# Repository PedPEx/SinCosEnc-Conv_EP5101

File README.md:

# EP5101 SinCos $11µA_{PP}$ and $1V_{PP}$ encoder/glass scale to TTL (RS422 compliance) converter (ARCHIVED)

This repo is no longer maintained. There is no reason to interface $11µA_{PP}$ sensors with the help of this PCB and an EtherCAT-based incremental encoder input module - like an EL5101 or an EP5101. Due to the cost of one assembled converter PCB (~30€ total), it is a competitive alternative to the original iC-Haus EVAL board of the [iC-NV](https://www.ichaus.de/product/ic-nv/) and the Heidenhain EXEs, if used with other RS422 or TTL encoder inputs.

If you are planning on using EtherCAT as your system bus, use the [documented process here on how to modify an EL5021 terminal](https://github.com/PedPEx/EL5021_multi-signal-mod) instead (which internally uses an iC-Haus IC similar to this project).

In my [bachelor's thesis](https://pedpex.github.io/Maho400E-LinuxCNC/docs/bachelors_thesis.pdf) I updated the old 0.9.6/0.9.7 version of the PCB a little, so that it better tolerates EMI conditions. As I was not very happy with the improvements in v0.9.8, it was never officially pushed. After further inspection, starting from scratch would be the better decision in order to get better EMI ratings. Additionally, the shielding of the EP5101-0011 is floating, which is also not the desired state. Since the alternative is far cheaper, a 4-layer redesign is not worthwhile, and as the new board is no longer used, this project will no longer be maintained and will therefore be archived.

PCB version v0.9.6 was fully working and successfully tested. Version v0.9.8 was never produced nor tested.
This board is provided as is - unfinished and untested. Productive use is explicitly not recommended! Further rework is required. No support is offered for it. The project will be left as is.

---

<details>
  <summary>Old README content</summary>
  
# EP5101 SinCos $11µA_{PP}$ and $1V_{PP}$ encoder/glass scale to TTL (RS422 compliance) converter (WIP!)
This interface board is designed to convert a encoder signal with $11µA_{PP}$ (peak-peak) or $1V_{PP}$ signal to TTL with a [iC-Haus iC-NV](https://www.ichaus.de/product/ic-nv/) be used with a [Beckhoff EP5101](https://www.beckhoff.com/de-de/produkte/i-o/ethercat-box/epxxxx-industriegehaeuse/ep5xxx-winkel-wegmessung/ep5101-0011.html?) for example in LinuxCNC.

Assembly concept (with old potentiometer and RJ45 jack):

Single encoder input             |  Three encoder inputs with terminal blocks
:-------------------------:|:-------------------------:
  |  

PCB:\

## ToDo
- ✅ finished prototype PCB (v0.9.6)
- ✅ working conversion
- ✅ tested intensively with [LS403](docs/Heidenhain-LS-403-LS-403C.pdf) and [EP5101](https://www.beckhoff.com/de-de/produkte/i-o/ethercat-box/epxxxx-industriegehaeuse/ep5xxx-winkel-wegmessung/ep5101-0011.html?)

## Powering, connectors and signals
The board needs no seperate supply voltage and is fully powered by the 5V supply of the EP5101. The green led indicates a working 5V sensor rail. Supported input signals are $11µA_{PP}$ (standard) and $1V_{PP}$. By default, the output is a differential RS422 TTL-encoder signal. In that case, component ```U2``` ([AM26LS31](https://www.ti.com/product/de-de/AM26LS31) - Differential Line Driver) is populated on the PCB. By removing ```U2``` and either manualy shorting ```JP1 - JP6``` or populating ```R5 - R10``` with $0 \Omega$ resistors (manual adjustment of BOM is required). 

Because the [Beckhoff EL5101](https://www.beckhoff.com/de-de/produkte/i-o/ethercat-klemmen/el5xxx-winkel-wegmessung/el5101.html) is way more common than the EP5101, a 3D printable holder is in the works and will also be added to the repo, as soon as it has reached a usable state. 

There could also be a master-PCB, which would be used in standalone use or with a Mesa FPGA board. This master-PCB would need a 24V to 5V regulator and three DSUB15 female connectors in order to connect to the interpolator PCBs and three connectors (RJ45 eventually?) to connect the TTL signals to the Mesa encoder inputs. A integrated DIN rail mount would make mounting easy. In case there is interest in such a board, feel free to open a issue and i will design one. 

## Mounting adaptor
There is a DIN-rail mounting adaptor avaliable, which is used to mount a M23 male connector and a EP5101 onto a 35 mm standard rail. You can find the [files to 3D print](https://than.gs/m/1345234) it yourself over on my Thangs-account.

## Config switches
Pretty much everything of the [iC-NV](https://www.ichaus.de/product/ic-nv/) is configurable through config switches and a potentiometer ($50 k\Omega$). The two most common configs are printed on the backside of the PCB

## Terminal blocks, connectors and pinouts
The shielded DSUB15 port has the following pinout:

| pin DSUB15 | usage/signal |
| :---  | :---      |
| 1     | DifSig_A+ / TTL_A   |
| 2     | GND   |
| 3     | DifSig_B+ / TTL_B   |
| 4     | 5V VCC   |
| 5     | n.c.   |
| 6     | n.c.       |
| 7     | DifSig_C- / TTL_GND  |
| 8     | n.c.  |
| 9     | DifSig_A- / TTL_GND  |
| 10    | GND  |
| 11    | DifSig_B- / TTL_GND  |
| 12    | 5V VCC  |
| 13    | E̅R̅R̅O̅R̅ out |
| 14    | DifSig_C+ / TTL_B  |
| 15    | n.c.  |

The shielded RJ45 port has the following pinout:

| pin RJ45 | usage/signal |
| :---  | :---      |
| 1     | In_SIN+   |
| 2     | In_SIN-   |
| 3     | +5 V      |
| 4     | In_COS+   |
| 5     | In_COS-   |
| 6     | GND       |
| 7     | In_ZERO+  |
| 8     | In_ZERO-  |

The 8 pin male-header J2 has the following pinout (standard Heidenhain pinout):

```
                        odd pins  |  even pins
╔════╦════╗             ----------|------------
║  1 ║  2 ║════════      In_SIN+  |  In_SIN-
╠════╬════╣                       |
║  3 ║  4 ║════════      In_COS+  |  In_COS-
╠════╬════╣                       |
║  5 ║  6 ║════════     In_ZERO+  |  In_ZERO-
╠════╬════╣                       |
║  7 ║  8 ║════════          GND  |  Shield
╠════╬════╣                       |
║  9 ║ 10 ║════════          +5V  |  Shield
╚════╩════╝
```

*Note:*\
DO ONLY CONNECT ONE SENSOR INPUT! NEVER USE THE PINHEADER AND RJ45 SIMULTANEOUSLY!

## Analog Frontend / Signal Conditioning Stage
After reaching out to iC-Haus' support for some details about the needed analog frontend for $11 µA_{PP}$ sensors, i got some details on how to implement it. A really nice solution which works with $1 V_{PP}$ as well as $11 µA_{PP}$ signals was documented in the [iC-NQC datasheet (page 28)](docs/iC-NQC_datasheet_E2en.pdf). This exact signal conditioning stage was implemented for all three stages. By shorting each ```CHx_JP1``` you can connect the $120 \Omega$ termination resistor to the input side of the input stage and by that set the device to its $1 V_{PP}$ operating mode.

## Usage/Software
This interface board is meant to be used in combination with the [Beckhoff EP5101 module](hhttps://www.beckhoff.com/de-de/produkte/i-o/ethercat-box/epxxxx-industriegehaeuse/ep5xxx-winkel-wegmessung/ep5101-0011.html?). The EP5101 is then used by the [LinuxCNC software](https://linuxcnc.org/) to read e.g. Heidenhain LS403 glass scales on a Maho MH400E.

A adaptor/mounting kit is in the works, that this project can also be used with [Beckhoffs EL5101](https://www.beckhoff.com/de-de/produkte/i-o/ethercat-klemmen/el5xxx-winkel-wegmessung/el5101.html) encoder inputs.

Also keep in mind that you need a sufficiently sized counter. For most retrofits a 16 bit wide counter will not cut it. 
Quick example:
```math 
n_{min} = \log_2 \left(\frac{range\_of\_motion}{axis\_resolution}\right) = \log_2 \left(\frac{400 mm}{1 \mu m}\right) = 18.61 bit \approx \textbf{19 bit > 16 bit}
```
In addition to the resolution you you also need to check the cutoff frequency (maximum input frequency) of the encoder input. The ```EP5101-0011``` for example is limited to $1.0 MHz$ (that's really high, especally in fourfold evaluation mode). For a resolution of $1 µm$ the maximum axis speed is:
```math
v_{max\_EC-Input} = \frac{resolution\_of\_sensor}{interpolation\_factor \cdot quadratur\_encoder\_input} \cdot cutoff\_frequency = {overall\_resolution \cdot cutoff\_frequency} = \frac{20µm}{5 \cdot 4} \cdot 1.0 MHz = 1µm \cdot 1.0 MHz = 1.0 \frac{m}{s}
```
The same calculation needs to be done with the input side of the IC ```iC-NV```. The cutoff frequency depends on the used gain. For a $gain = 4$ the manual states a $fin_{MAX}=200 kHz$ (for RCLK = VCC).
```math
v_{max\_IC-Input} = resolution\_of\_sensor \cdot cutoff\_frequency_{IC} = 20µm \cdot 200 kHz = 4.0 \frac{m}{s}
```
The lower value of the two calculated velocities, $v_{max\_{EC-Input}} = 1.0 \frac{m}{s}$ and $v_{max\_IC-Input} = 4.0 \frac{m}{s}$, is $1.0 \frac{m}{s}$. This represents the maximum permissible speed for the corresponding axis and must not be exceeded!

## Documentation
All docs can be found in the [docs folder](docs/).

## Online Preview / BOM
[Detailed schematics preview](https://kicanvas.org/?github=https%3A%2F%2Fgithub.com%2FPedPEx%2FSinCosEnc-Conv_EP5101) (KiCanvas)

[Online BOM](https://htmlpreview.github.io/?https://raw.githubusercontent.com/PedPEx/SinCosEnc-Conv_EP5101/master/bom/webviewer-BOM.html)

[PDF schematics (v0.9.6)](https://github.com/PedPEx/SinCosEnc-Conv_EP5101/blob/master/SinCosEnc-Converter_EP5101-0011_schematic_v0.9.6.pdf)

## *Note*
The pictures were rendered with the help of Blender and the [pcb2blender](https://github.com/30350n/pcb2blender) plugin and the HTML BOM was created with [InteractiveHtmlBom](https://github.com/openscopeproject/InteractiveHtmlBom).

</details>

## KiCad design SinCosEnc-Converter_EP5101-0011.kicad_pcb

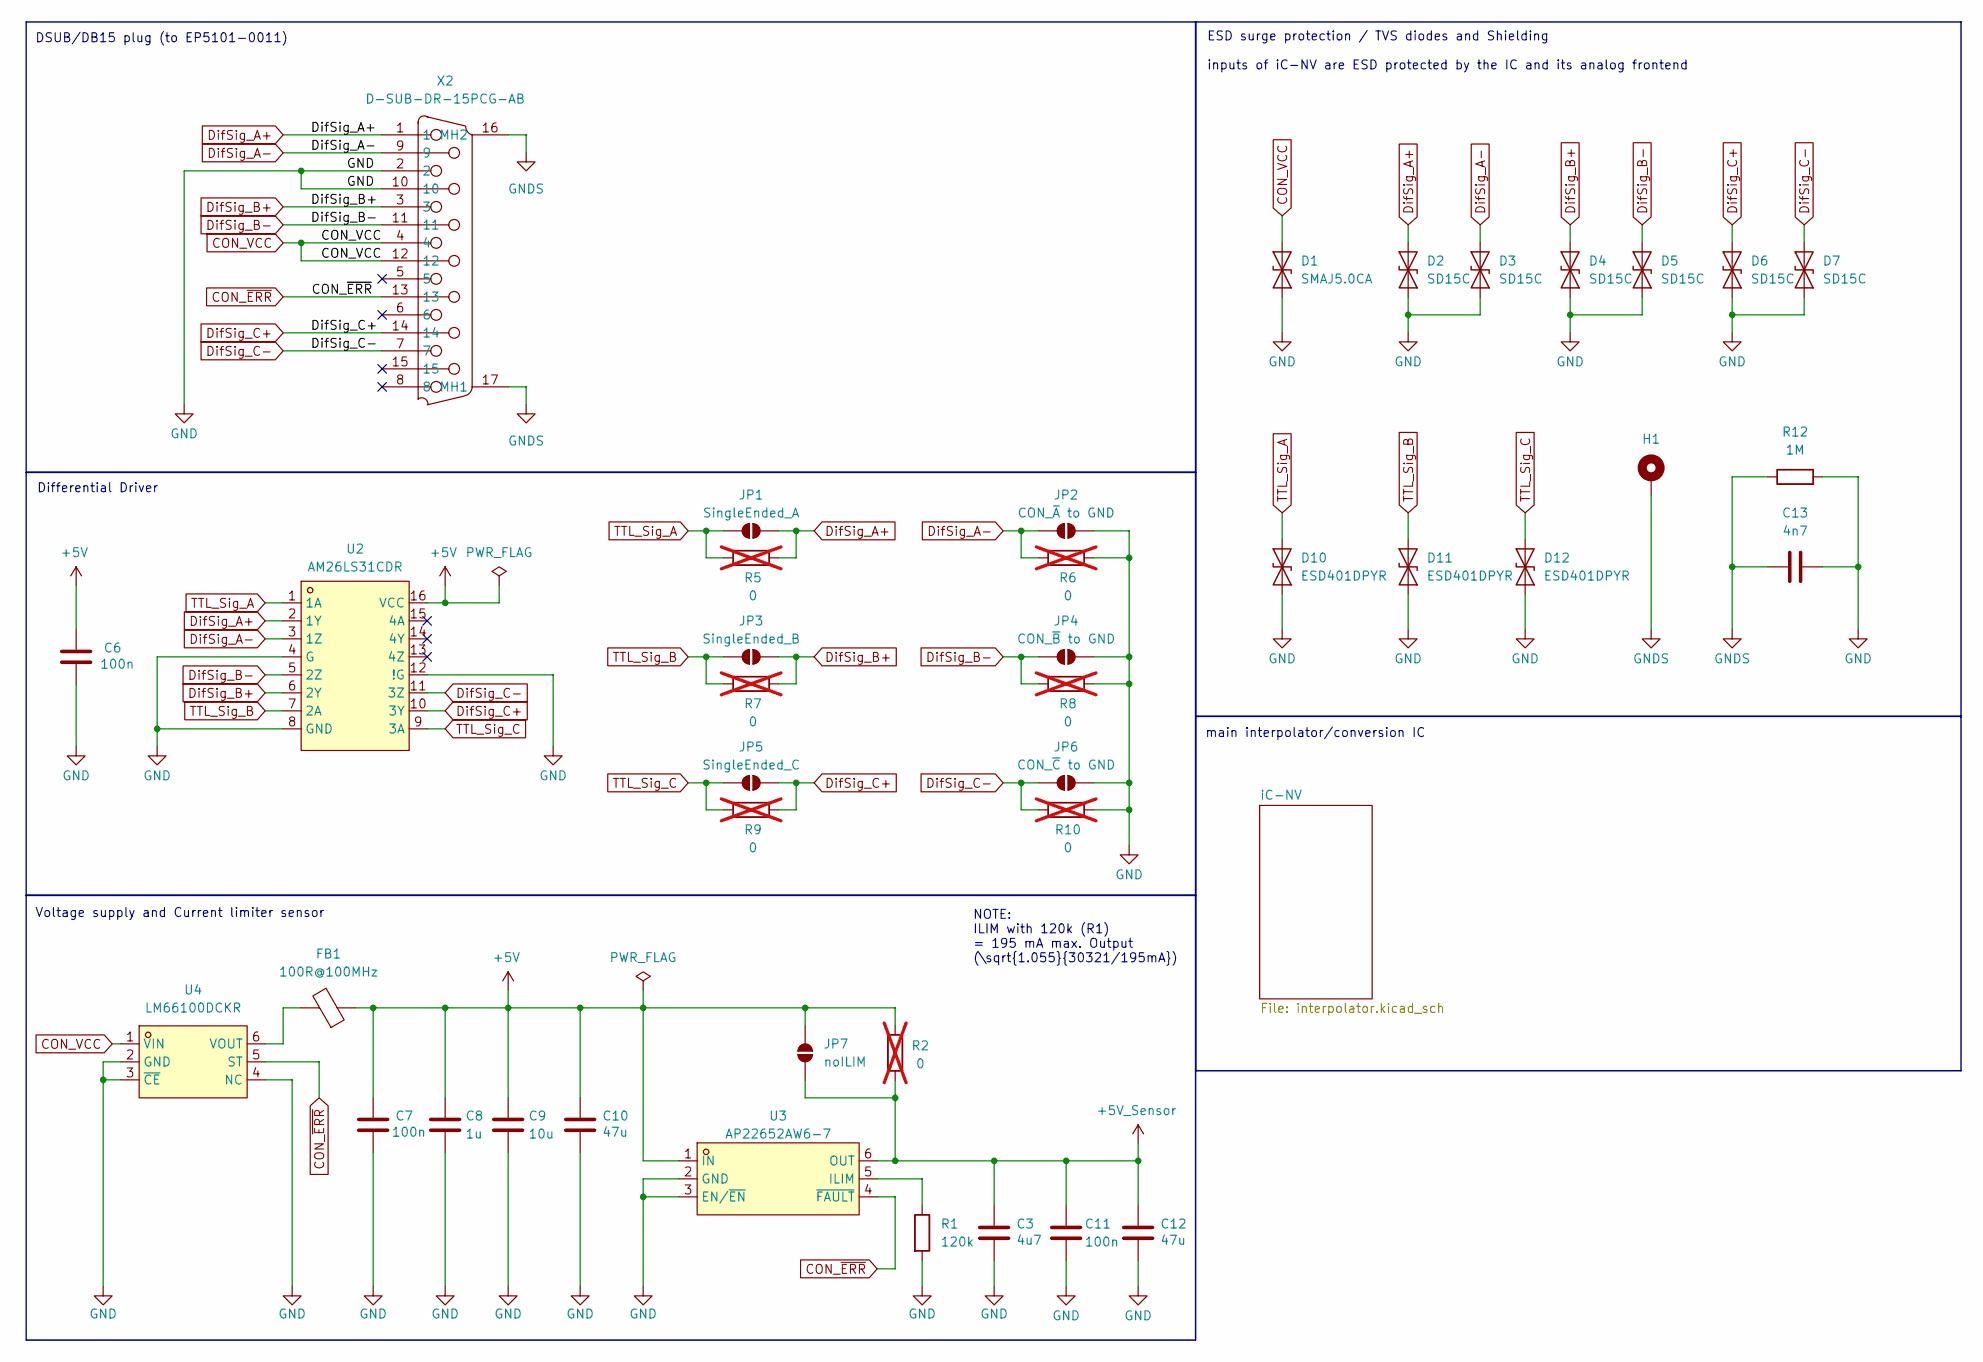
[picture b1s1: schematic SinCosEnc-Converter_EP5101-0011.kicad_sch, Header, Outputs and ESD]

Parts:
C3: 4u7; C_0603_1608Metric; LCSC Part C1705
C6, C7, C11: 100n; C_0603_1608Metric; LCSC Part C14663
C8: 1u; C_0603_1608Metric; LCSC Part C15849
C9: 10u; C_0603_1608Metric; LCSC Part C91606
C10, C12: 47u; C_1206_3216Metric; LCSC Part C94034
C13: 4n7; C_1808_4520Metric; LCSC Part C161101
D1: SMAJ5.0CA; D_SMA; LCSC Part C83324
D2, D3, D4, D5, D6, D7: SD15C; D_SOD-323; LCSC Part C207245
D10, D11, D12: ESD401DPYR; Texas_DPY0002A_0.6x1mm_P0.65mm; LCSC Part C1974752
FB1: 100R@100MHz; L0603; LCSC Part C107332
H1: MountingHole_Pad; MountingHole_3.2mm_M3_DIN965_Pad_TopBottom
JP1: SingleEnded_A; SolderJumper-2_P1.3mm_Open_RoundedPad1.0x1.5mm
JP2: CON_~{A} to GND; SolderJumper-2_P1.3mm_Open_RoundedPad1.0x1.5mm
JP3: SingleEnded_B; SolderJumper-2_P1.3mm_Open_RoundedPad1.0x1.5mm
JP4: CON_~{B} to GND; SolderJumper-2_P1.3mm_Open_RoundedPad1.0x1.5mm
JP5: SingleEnded_C; SolderJumper-2_P1.3mm_Open_RoundedPad1.0x1.5mm
JP6: CON_~{C} to GND; SolderJumper-2_P1.3mm_Open_RoundedPad1.0x1.5mm
JP7: noILIM; SolderJumper-2_P1.3mm_Open_RoundedPad1.0x1.5mm
R1: 120k; R_0603_1608Metric; LCSC Part C22954
R2, R5, R6, R7, R8, R9, R10: 0; R_0603_1608Metric; not fitted
R12: 1M; R_2010_5025Metric; LCSC Part C2779367
U2: AM26LS31CDR; SOIC-16_L9.9-W3.9-P1.27-LS6.0-BL; LCSC Part C6179
U3: AP22652AW6-7; SOT-23-6_L2.9-W1.6-P0.95-LS2.8-BL; LCSC Part C5329413
U4: LM66100DCKR; SC-70-6_L2.0-W1.3-P0.65-LS2.1-BL; LCSC Part C2869734
X2: D-SUB-DR-15PCG-AB; DSUB-TH_D-SUB-DR-15PCG-AB; LCSC Part C19077347

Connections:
+5V: C6.2, C7.2, C8.2, C9.2, C10.2, FB1.1, JP7.2 (B), R2.2, U2.16 (VCC), U3.1 (IN); also elsewhere on the board
+5V_Sensor: C3.2, C11.2, C12.2, JP7.1 (A), R2.1, U3.6 (OUT); also elsewhere on the board
CON_VCC: D1.2 (A2), U4.1 (VIN), X2.4, X2.12
CON_~ERR: U3.4 (~FAULT), U4.5 (ST), X2.13; also elsewhere on the board
DifSig_A+: D2.2 (A2), JP1.2 (B), R5.1, U2.2 (1Y), X2.1
DifSig_A-: D3.2 (A2), JP2.1 (A), R6.2, U2.3 (1Z), X2.9
DifSig_B+: D4.2 (A2), JP3.2 (B), R7.1, U2.6 (2Y), X2.3
DifSig_B-: D5.2 (A2), JP4.1 (A), R8.2, U2.5 (2Z), X2.11
DifSig_C+: D6.2 (A2), JP5.2 (B), R9.1, U2.10 (3Y), X2.14
DifSig_C-: D7.2 (A2), JP6.1 (A), R10.2, U2.11 (3Z), X2.7
GND: C3.1, C6.1, C7.1, C8.1, C9.1, C10.1, C11.1, C12.1, C13.2, D1.1 (A1), D2.1 (A1), D3.1 (A1), D4.1 (A1), D5.1 (A1), D6.1 (A1), D7.1 (A1), D10.1 (A1), D11.1 (A1), D12.1 (A1), JP2.2 (B), JP4.2 (B), JP6.2 (B), R1.2, R6.1, R8.1, R10.1, R12.2, U2.4 (G), U2.8 (GND), U2.12 (!G), U3.2 (GND), U3.3 (EN/~EN), U4.2 (GND), U4.3 (~CE), U4.4 (NC), X2.2, X2.10; also elsewhere on the board
GNDS: C13.1, H1.1, R12.1, X2.16 (MH2), X2.17 (MH1); also elsewhere on the board
unnamed: R1.1, U3.5 (ILIM)
unnamed: FB1.2, U4.6 (VOUT)
TTL_Sig_A: D10.2 (A2), JP1.1 (A), R5.2, U2.1 (1A); also elsewhere on the board
TTL_Sig_B: D11.2 (A2), JP3.1 (A), R7.2, U2.7 (2A); also elsewhere on the board
TTL_Sig_C: D12.2 (A2), JP5.1 (A), R9.2, U2.9 (3A); also elsewhere on the board

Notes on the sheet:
main interpolator/conversion IC
NOTE: ILIM with 120k (R1) = 195 mA max. Output (\sqrt{1.055}{30321/195mA})
ESD surge protection / TVS diodes and Shielding inputs of iC-NV are ESD protected by the IC and its analog frontend
Voltage supply and Current limiter sensor
DSUB/DB15 plug (to EP5101-0011)
Differential Driver

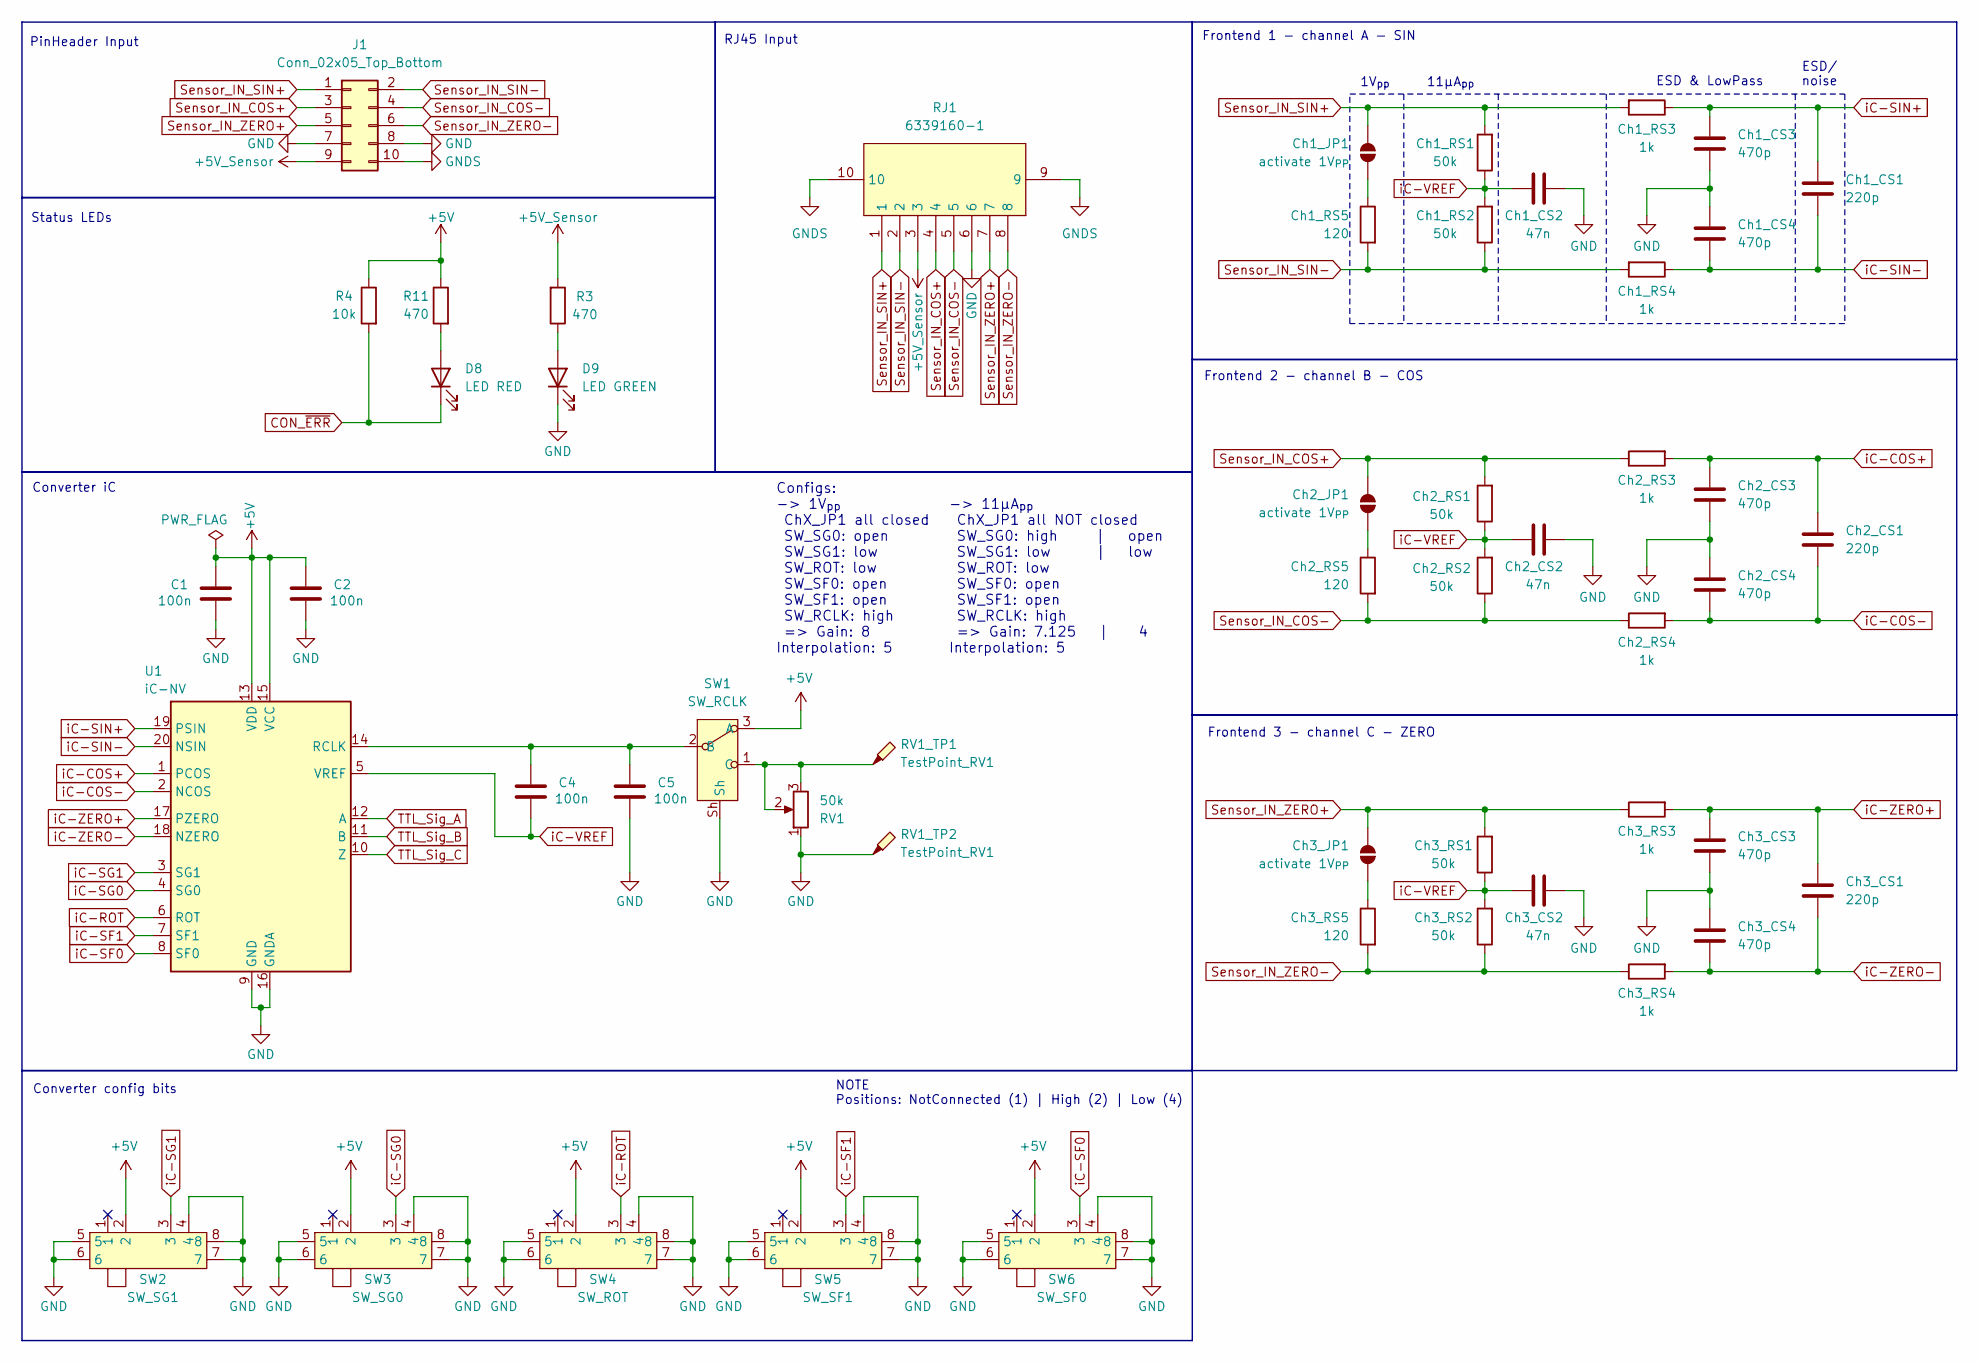
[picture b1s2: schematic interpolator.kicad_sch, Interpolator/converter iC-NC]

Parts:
C1, C2, C4, C5: 100n; C_0603_1608Metric; LCSC Part C14663
Ch1_CS1, Ch2_CS1, Ch3_CS1: 220p; C_0603_1608Metric; LCSC Part C107081
Ch1_CS2, Ch2_CS2, Ch3_CS2: 47n; C_0603_1608Metric; LCSC Part C1622
Ch1_CS3, Ch1_CS4, Ch2_CS3, Ch2_CS4, Ch3_CS3, Ch3_CS4: 470p; C_0603_1608Metric; LCSC Part C22396
Ch1_JP1, Ch2_JP1, Ch3_JP1: activate 1V_{PP}; SolderJumper-2_P1.3mm_Open_RoundedPad1.0x1.5mm
Ch1_RS1, Ch1_RS2, Ch2_RS1, Ch2_RS2, Ch3_RS1, Ch3_RS2: 50k; R_0603_1608Metric; LCSC Part C861451
Ch1_RS3, Ch1_RS4, Ch2_RS3, Ch2_RS4, Ch3_RS3, Ch3_RS4: 1k; R_0603_1608Metric
Ch1_RS5, Ch2_RS5, Ch3_RS5: 120; R_0603_1608Metric; LCSC Part C22787
D8: LED RED; LED_0603_1608Metric; LCSC Part C2986060
D9: LED GREEN; LED_0603_1608Metric; LCSC Part C2986059
J1: Conn_02x05_Top_Bottom; PinHeader_2x05_P2.54mm_Horizontal; LCSC Part C492433
R3, R11: 470; R_0603_1608Metric
R4: 10k; R_0603_1608Metric
RJ1: 6339160-1; RJ45-SMD_6339160-1; LCSC Part C125076
RV1: 50k; Potentiometer_Bourns_3266X_Horizontal; LCSC Part C780222
RV1_TP1: TestPoint_RV1; TestPoint_THTPad_2.0x2.0mm_Drill1.0mm
RV1_TP2: TestPoint_RV1; TestPoint_THTPad_D2.0mm_Drill1.0mm
SW1: SW_RCLK; SW-SMD_XKB_SS-3292S-L2-W; LCSC Part C2884756
SW2: SW_SG1; SW-SMD_MSK13C02-BB; LCSC Part C5149819
SW3: SW_SG0; SW-SMD_MSK13C02-BB; LCSC Part C5149819
SW4: SW_ROT; SW-SMD_MSK13C02-BB; LCSC Part C5149819
SW5: SW_SF1; SW-SMD_MSK13C02-BB; LCSC Part C5149819
SW6: SW_SF0; SW-SMD_MSK13C02-BB; LCSC Part C5149819
U1: iC-NV; TSSOP-20_4.4x6.5mm_P0.65mm

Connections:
+5V: C1.2, C2.2, R4.1, R11.1, SW1.3 (A), SW2.2, SW3.2, SW4.2, SW5.2, SW6.2, U1.13 (VDD), U1.15 (VCC); also elsewhere on the board
+5V_Sensor: J1.9, R3.2, RJ1.3; also elsewhere on the board
CON_~ERR: D8.1 (K), R4.2; also elsewhere on the board
GND: C1.1, C2.1, C5.1, Ch1_CS2.2, Ch1_CS3.2, Ch1_CS4.1, Ch2_CS2.2, Ch2_CS3.2, Ch2_CS4.1, Ch3_CS2.2, Ch3_CS3.2, Ch3_CS4.1, D9.1 (K), J1.7, J1.8, RJ1.6, RV1.1, RV1_TP2.1, SW1.Sh, SW2.4, SW2.5, SW2.6, SW2.7, SW2.8, SW3.4, SW3.5, SW3.6, SW3.7, SW3.8, SW4.4, SW4.5, SW4.6, SW4.7, SW4.8, SW5.4, SW5.5, SW5.6, SW5.7, SW5.8, SW6.4, SW6.5, SW6.6, SW6.7, SW6.8, U1.9 (GND), U1.16 (GNDA); also elsewhere on the board
GNDS: J1.10, RJ1.9, RJ1.10; also elsewhere on the board
unnamed: Ch1_JP1.1 (A), Ch1_RS5.1
unnamed: Ch2_JP1.1 (A), Ch2_RS5.1
unnamed: Ch3_JP1.1 (A), Ch3_RS5.1
unnamed: D8.2 (A), R11.2
unnamed: D9.2 (A), R3.1
unnamed: C4.2, C5.2, SW1.2 (B), U1.14 (RCLK)
unnamed: RV1.2, RV1.3, RV1_TP1.1, SW1.1 (C)
Sensor_IN_COS+: Ch2_JP1.2 (B), Ch2_RS1.2, Ch2_RS3.1, J1.3, RJ1.4
Sensor_IN_COS-: Ch2_RS2.1, Ch2_RS4.1, Ch2_RS5.2, J1.4, RJ1.5
Sensor_IN_SIN+: Ch1_JP1.2 (B), Ch1_RS1.2, Ch1_RS3.2, J1.1, RJ1.1
Sensor_IN_SIN-: Ch1_RS2.1, Ch1_RS4.2, Ch1_RS5.2, J1.2, RJ1.2
Sensor_IN_ZERO+: Ch3_JP1.2 (B), Ch3_RS1.2, Ch3_RS3.1, J1.5, RJ1.7
Sensor_IN_ZERO-: Ch3_RS2.1, Ch3_RS4.1, Ch3_RS5.2, J1.6, RJ1.8
TTL_Sig_A: U1.12 (A); also elsewhere on the board
TTL_Sig_B: U1.11 (B); also elsewhere on the board
TTL_Sig_C: U1.10 (Z); also elsewhere on the board
iC-COS+: Ch2_CS1.1, Ch2_CS3.1, Ch2_RS3.2, U1.1 (PCOS)
iC-COS-: Ch2_CS1.2, Ch2_CS4.2, Ch2_RS4.2, U1.2 (NCOS)
iC-ROT: SW4.3, U1.6 (ROT)
iC-SF0: SW6.3, U1.8 (SF0)
iC-SF1: SW5.3, U1.7 (SF1)
iC-SG0: SW3.3, U1.4 (SG0)
iC-SG1: SW2.3, U1.3 (SG1)
iC-SIN+: Ch1_CS1.1, Ch1_CS3.1, Ch1_RS3.1, U1.19 (PSIN)
iC-SIN-: Ch1_CS1.2, Ch1_CS4.2, Ch1_RS4.1, U1.20 (NSIN)
iC-VREF: C4.1, Ch1_CS2.1, Ch1_RS1.1, Ch1_RS2.2, Ch2_CS2.1, Ch2_RS1.1, Ch2_RS2.2, Ch3_CS2.1, Ch3_RS1.1, Ch3_RS2.2, U1.5 (VREF)
iC-ZERO+: Ch3_CS1.1, Ch3_CS3.1, Ch3_RS3.2, U1.17 (PZERO)
iC-ZERO-: Ch3_CS1.2, Ch3_CS4.2, Ch3_RS4.2, U1.18 (NZERO)

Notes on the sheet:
Frontend 3 - channel C - ZERO
Converter config bits
Status LEDs
Frontend 1 - channel A - SIN
Frontend 2 - channel B - COS
RJ45 Input
Converter iC
11µA_{pp}
-> 11µA_{pp} ChX_JP1 all NOT closed SW_SG0: high | open SW_SG1: low | low SW_ROT: low SW_SF0: open SW_SF1: open SW_RCLK: high => Gain: 7.125 | 4 Interpolation: 5
NOTE Positions: NotConnected (1) | High (2) | Low (4)
ESD/ noise
PinHeader Input
Configs: -> 1V_{pp} ChX_JP1 all closed SW_SG0: open SW_SG1: low SW_ROT: low SW_SF0: open SW_SF1: open SW_RCLK: high => Gain: 8 Interpolation: 5
1V_{pp}
ESD & LowPass

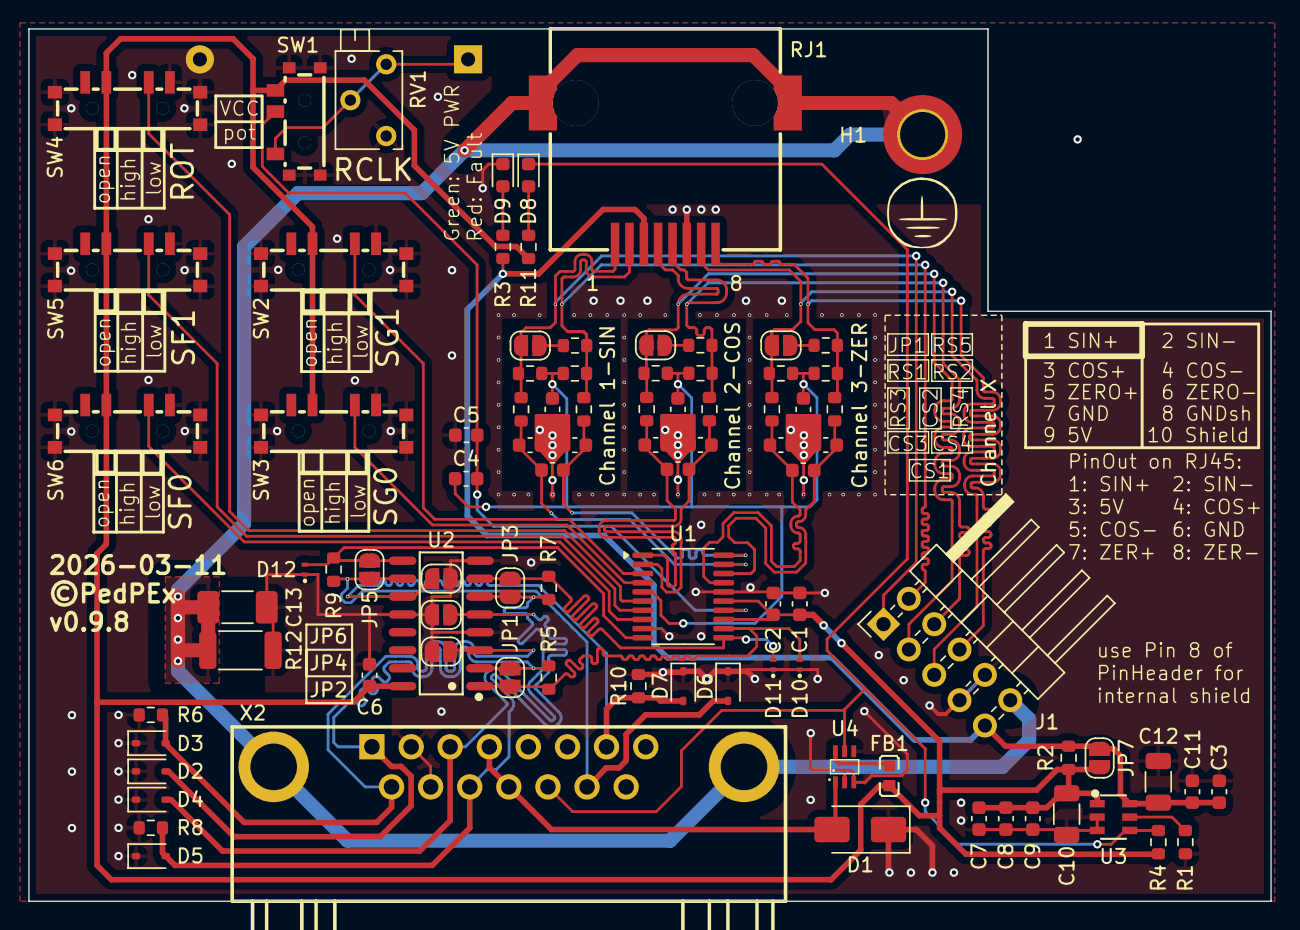
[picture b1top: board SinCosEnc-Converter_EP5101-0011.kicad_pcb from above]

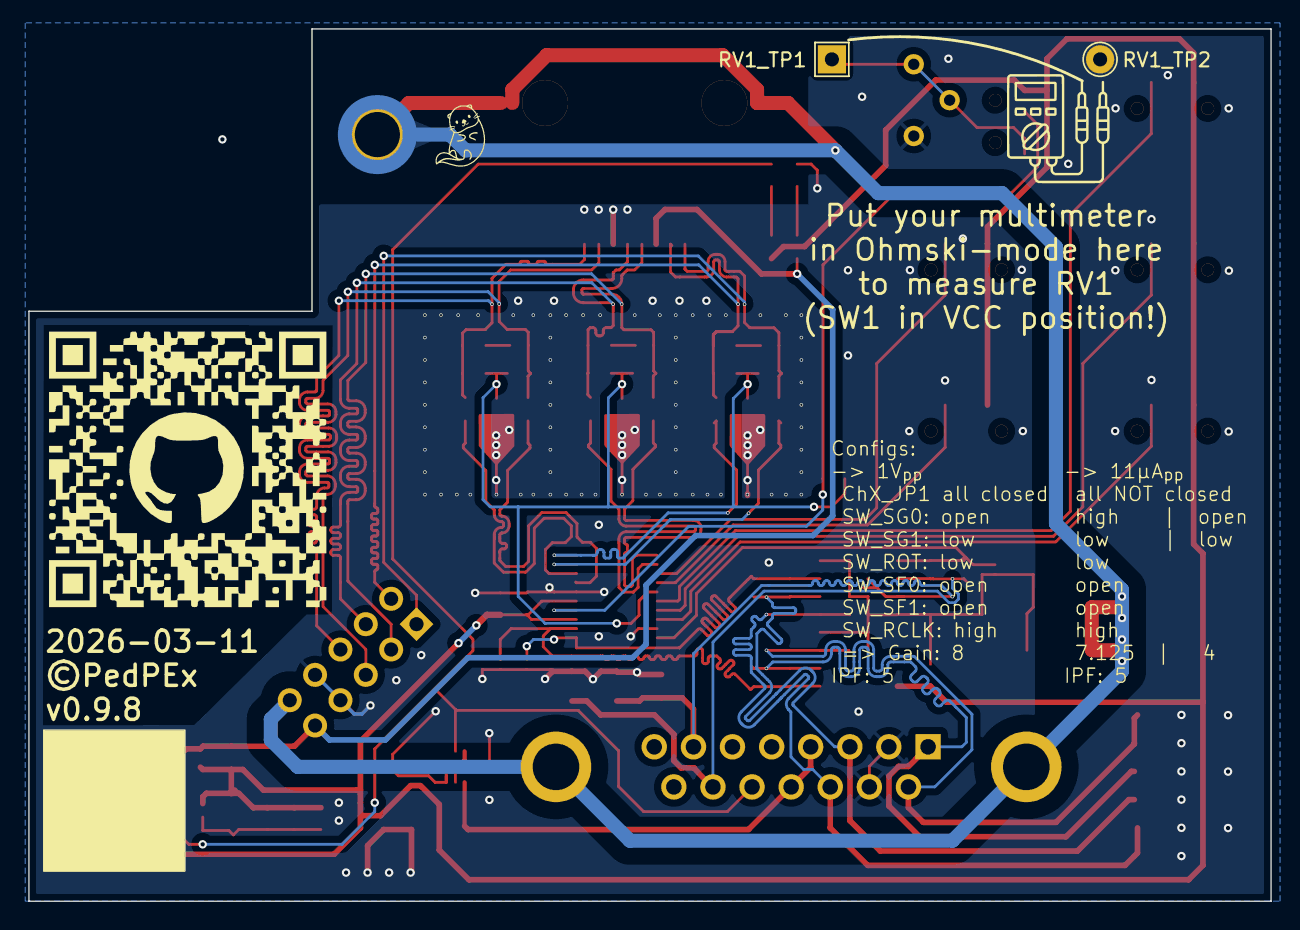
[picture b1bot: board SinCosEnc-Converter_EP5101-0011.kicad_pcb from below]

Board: 2 copper layers, 88.0 x 61.8 mm, 92 parts (2 on the bottom side), 42 nets.

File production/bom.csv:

Designator,Footprint,Quantity,Value,LCSC Part #
"C1, C2, C4, C5, C6, C7",0603,6,100n,
"C10, C12",1206,2,47u,C94034
C11,0603,1,0.1u,
C13,1808,1,4n7,C161101
C3,0603,1,4u7,C1705
C8,0603,1,1u,
C9,0603,1,10u,
"Ch1_CS1, Ch2_CS1, Ch3_CS1",0603,3,220p,
"Ch1_CS2, Ch2_CS2, Ch3_CS2",0603,3,47n,
"Ch1_CS3, Ch1_CS4, Ch2_CS3, Ch2_CS4, Ch3_CS3, Ch3_CS4",0603,6,470p,
"Ch1_RS1, Ch1_RS2, Ch2_RS1, Ch2_RS2, Ch3_RS1, Ch3_RS2",0603,6,50k,C861451
"Ch1_RS3, Ch1_RS4, Ch2_RS3, Ch2_RS4, Ch3_RS3, Ch3_RS4",0603,6,1k,
"Ch1_RS5, Ch2_RS5, Ch3_RS5",0603,3,120,
D1,D_SMA,1,SMAJ5.0CA,C83324
"D10, D11, D12",Texas_DPY0002A_0.6x1mm_P0.65mm,3,ESD401DPYR,C1974752
"D2, D3, D4, D5, D6, D7",D_SOD-323,6,SD15,C207245
D8,0603,1,LED RED,C2986060
D9,0603,1,LED GREEN,C2986059
FB1,L0603,1,100R@100MHz,C107332
J1,PinHeader_2x05_P2.54mm_Horizontal,1,Conn_02x05_Top_Bottom,C492433
R1,0603,1,215k,C22954
"R10, R2, R5, R6, R7, R8, R9",0603,7,0,
"R11, R3",0603,2,470,
R12,2010,1,1M,C2779367
R4,0603,1,10k,
RJ1,RJ45-SMD_6339160-1,1,6339160-1,C125076
RV1,Potentiometer_Bourns_3266X_Horizontal,1,50k,C780222
RV1_TP1,TestPoint_THTPad_2.0x2.0mm_Drill1.0mm,1,TestPoint_RV1,
RV1_TP2,TestPoint_THTPad_D2.0mm_Drill1.0mm,1,TestPoint_RV1,
SW1,SW-SMD_XKB_SS-3292S-L2-W,1,SW_RCLK,C2884756
SW2,SW-SMD_MSK13C02-BB,1,SW_SG1,C5149819
SW3,SW-SMD_MSK13C02-BB,1,SW_SG0,C5149819
SW4,SW-SMD_MSK13C02-BB,1,SW_ROT,C5149819
SW5,SW-SMD_MSK13C02-BB,1,SW_SF1,C5149819
SW6,SW-SMD_MSK13C02-BB,1,SW_SF0,C5149819
U1,TSSOP-20_4.4x6.5mm_P0.65mm,1,iC-NV,
U2,SOIC-16_L9.9-W3.9-P1.27-LS6.0-BL,1,AM26LS31CDR,C6179
U3,SOT-23-6_L2.9-W1.6-P0.95-LS2.8-BL,1,AP22652AW6-7,C5329413
U4,SC-70-6_L2.0-W1.3-P0.65-LS2.1-BL,1,LM66100DCKR,C2869734
X2,DSUB-TH_D-SUB-DR-15PCG-AB,1,D-SUB-DR-15PCG-AB,C19077347

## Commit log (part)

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2025-05-18 init
2025-05-18 schematic finished ~90%, layout: just outline done added mounting concept pictures
2025-05-27 minor progress
2025-07-14 finished schematics for v0.9.0, PCB ToDo
2025-07-15 further ESD protection, PCB layout started
2025-07-16 v0.9.2 finished, board routed
2025-07-17 first theoretical working PCB finished (v0.9.3)
2025-07-18 cleaned up board layout -> v0.9.5 from v0.9.5 to v0.9.5 just minor optical improvements were done
2025-07-27 version 0.9.6 finished

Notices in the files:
SinCosEnc-Converter_EP5101-0011.kicad_pcb:
©PedPEx
